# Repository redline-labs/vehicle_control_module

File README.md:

# Vehicle Control Module

A communication gateway and power distribution for motorsports, serving as the main electronic hub of the vehicle.

## Goals
  - Completely open-source HW and SW.  Should be a platform that anybody can hack, extend, and make their own.
  - Common parts, readily available for Digikey, Mouser, etc.  Datasheets are available without NDA.
  - Shoot for OEM level reliability and robustness, without going full ASIL alphabet soup.

## Vision
  - Controlling a circuit should be as simple as writing some logic `(engine_temp_c > 70.0f) && (vehicle_speed_mps < 5.0f)`.
  - No need for traditional fuses, relays as something like a slow-blow fuse can be done in software.
  - Plug into the vehicle using standard ethernet to debug/reconfigure/reflash.
  - Foundation for support datalogging, telemetry, and HMI.

## Hardware
Based on the Microchip [ATSAMV71Q21](https://www.microchip.com/wwwproducts/en/ATSAMV71Q21).
* (2) CAN-FD channels via [TLE9250](https://www.infineon.com/cms/en/product/transceivers/automotive-transceiver/automotive-can-transceivers/tle9250xsj/).
* (3) 100BASE-T1 channels via [TJA1100](https://www.nxp.com/products/interfaces/ethernet-/automotive-ethernet-phy-transceivers/ieee-100base-t1-compliant-automotive-ethernet-phy-transceiver:TJA1100HN).
* (1) 100BASE-TX channel via [KSZ8061MNX](https://www.microchip.com/wwwproducts/en/KSZ8061) to support debug with a laptop.
* (18) High Side drivers via [BTS50015-1TAD](https://www.infineon.com/cms/en/product/power/smart-low-side-high-side-switches/automotive-smart-high-side-switch-profet/power-profet/bts50015-1tad/).
* (2) RS-232 serial channels to connect GPS receivers and legacy IMUs.
* (8) Digital Inputs.

## Prerequisites
### MacOS
```
wget https://armkeil.blob.core.windows.net/developer/Files/downloads/gnu-rm/10-2020q2/gcc-arm-none-eabi-10-2020-q2-preview-mac.pkg

# Install.  Add `/Applications/ARM/bin/` to PATH via bash_profile.

brew install cmake
```

## Building
```
# Jump into the sw directory, create a build dir, and then jump into that.
cd sw
mkdir build
cd build

# Run CMake specifying the toolchain file.
cmake ..

# Build!
make
```

## Debugging
A configuration script under `conf/j-link` can be used with Segger Ozone to load the generated ELF on target and debug.

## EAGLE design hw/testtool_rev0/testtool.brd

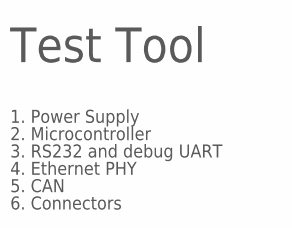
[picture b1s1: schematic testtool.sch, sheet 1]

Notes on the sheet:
Test Tool
1. Power Supply
2. Microcontroller
3. RS232 and debug UART
4. Ethernet PHY
5. CAN
6. Connectors

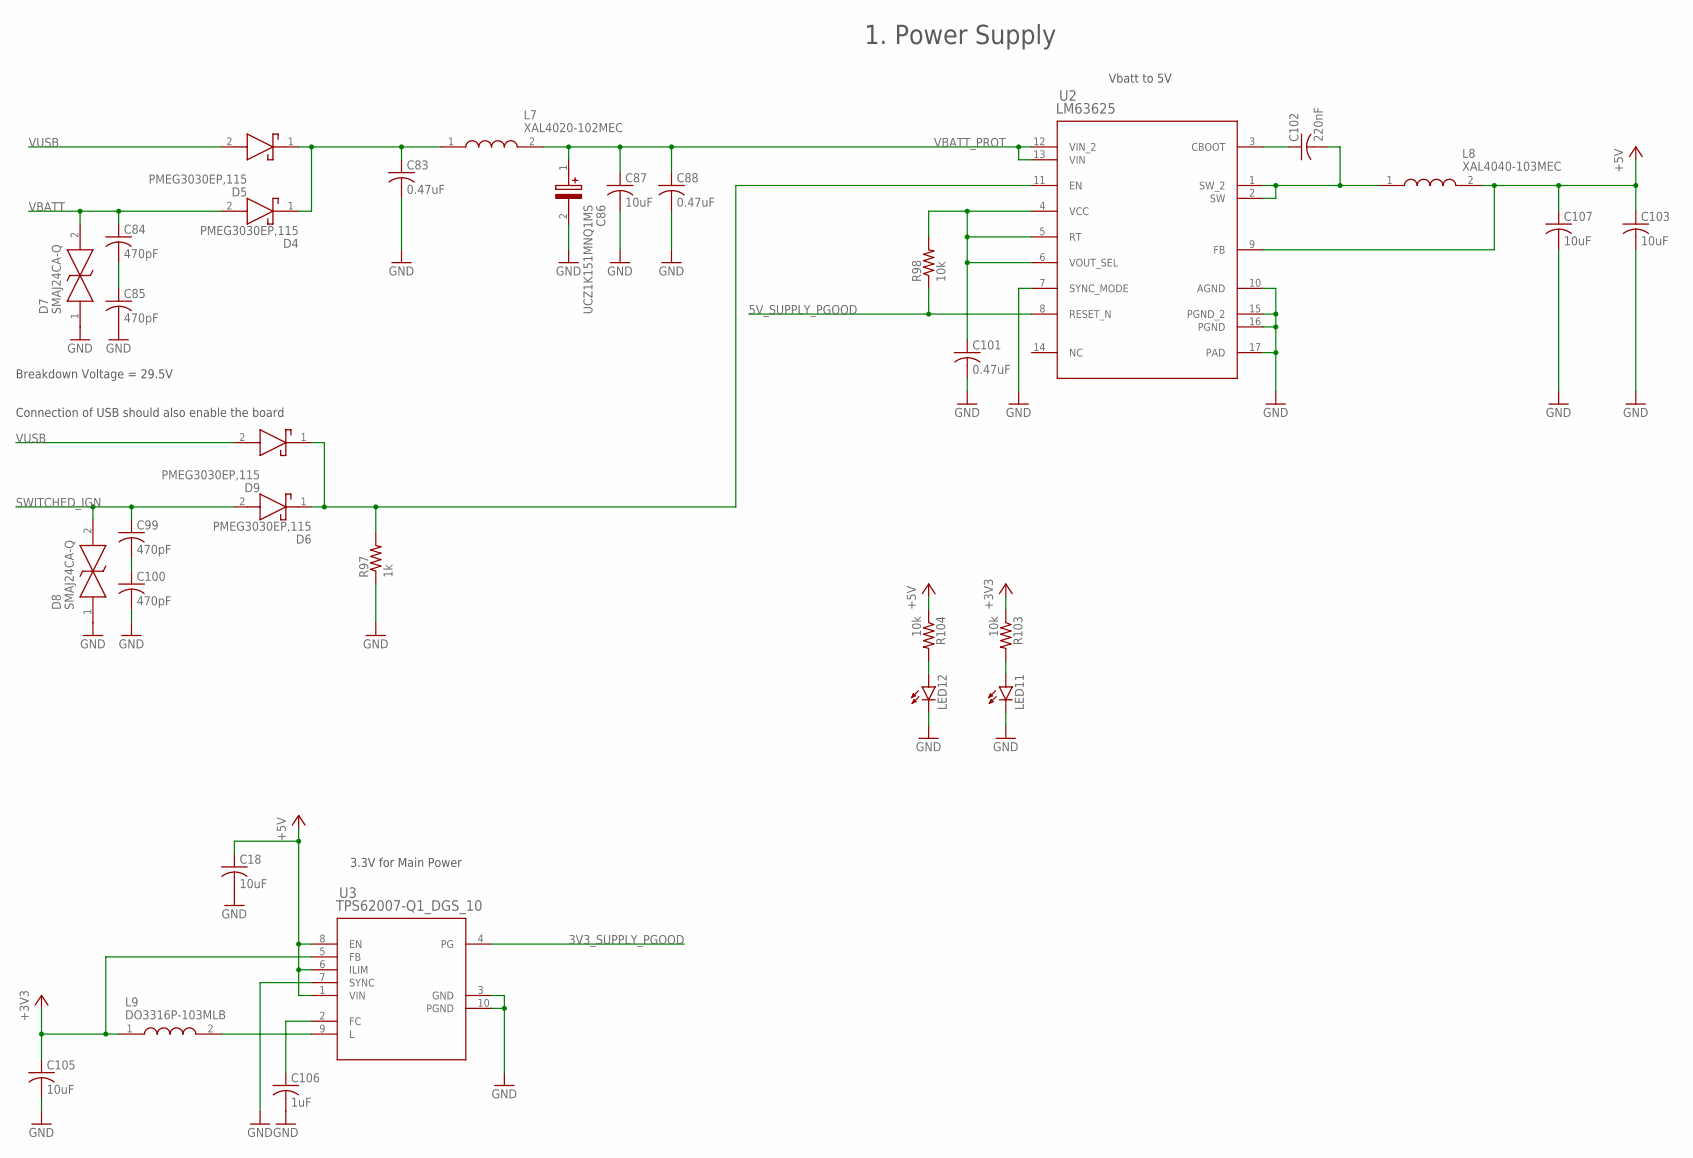
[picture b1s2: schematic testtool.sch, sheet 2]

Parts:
C18, C87, C103, C105, C107: 10uF; C0805
C83, C88: 0.47uF; C0805
C84, C85, C99, C100: 470pF; C0805
C86: UCZ1K151MNQ1MS; CAPAE1360X1450N
C101: 0.47uF; C0603
C102: 220nF; C0805
C106: 1uF; C0603
D4, D5, D6, D9: PMEG3030EP,115; SODFL4725X110N
D7, D8: SMAJ24CA-Q; DIONM5127X229N
L7: XAL4020-102MEC; XAL40XX
L8: XAL4040-103MEC; XAL40XX
L9: DO3316P-103MLB; DO3316P103MLB
LED11, LED12: LEDCHIPLED_0603; CHIPLED_0603
R97: 1k; R0805
R98, R103, R104: 10k; R0603
U2: LM63625; PWP0016K_L
U3: TPS62007-Q1_DGS_10; DGS10

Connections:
3V3_SUPPLY_PGOOD: U3.4 (PG); also elsewhere on the board
5V_SUPPLY_PGOOD: R98.1, U2.8 (RESET_N)
+3V3: C105.1, L9.1, R103.1, U3.5 (FB); also elsewhere on the board
+5V: C18.1, C103.1, C107.1, L8.2, R104.1, U2.9 (FB), U3.1 (VIN), U3.6 (ILIM), U3.8 (EN); also elsewhere on the board
GND: C18.2, C83.2, C85.2, C86.2 (-), C87.2, C88.2, C100.2, C101.2, C103.2, C105.2, C106.2, C107.2, D7.1, D8.1, LED11.C, LED12.C, R97.1, U2.7 (SYNC_MODE), U2.10 (AGND), U2.15 (PGND_2), U2.16 (PGND), U2.17 (PAD), U3.3 (GND), U3.7 (SYNC), U3.10 (PGND); also elsewhere on the board
unnamed: C99.2, C100.1
unnamed: D6.1 (K), D9.1 (K), R97.2, U2.11 (EN)
unnamed: C83.1, D4.1 (K), D5.1 (K), L7.1
unnamed: C84.2, C85.1
unnamed: C101.1, R98.2, U2.4 (VCC), U2.5 (RT), U2.6 (VOUT_SEL)
unnamed: L9.2, U3.9 (L)
unnamed: C102.2, L8.1, U2.1 (SW_2), U2.2 (SW)
unnamed: C106.1, U3.2 (FC)
unnamed: C102.1, U2.3 (CBOOT)
unnamed: LED11.A, R103.2
unnamed: LED12.A, R104.2
SWITCHED_IGN: C99.1, D6.2 (A), D8.2; also elsewhere on the board
VBATT: C84.1, D4.2 (A), D7.2; also elsewhere on the board
VBATT_PROT: C86.1 (+), C87.1, C88.1, L7.2, U2.12 (VIN_2), U2.13 (VIN)
VUSB: D5.2 (A), D9.2 (A); also elsewhere on the board

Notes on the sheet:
1. Power Supply
Vbatt to 5V
3.3V for Main Power
Breakdown Voltage = 29.5V
Connection of USB should also enable the board

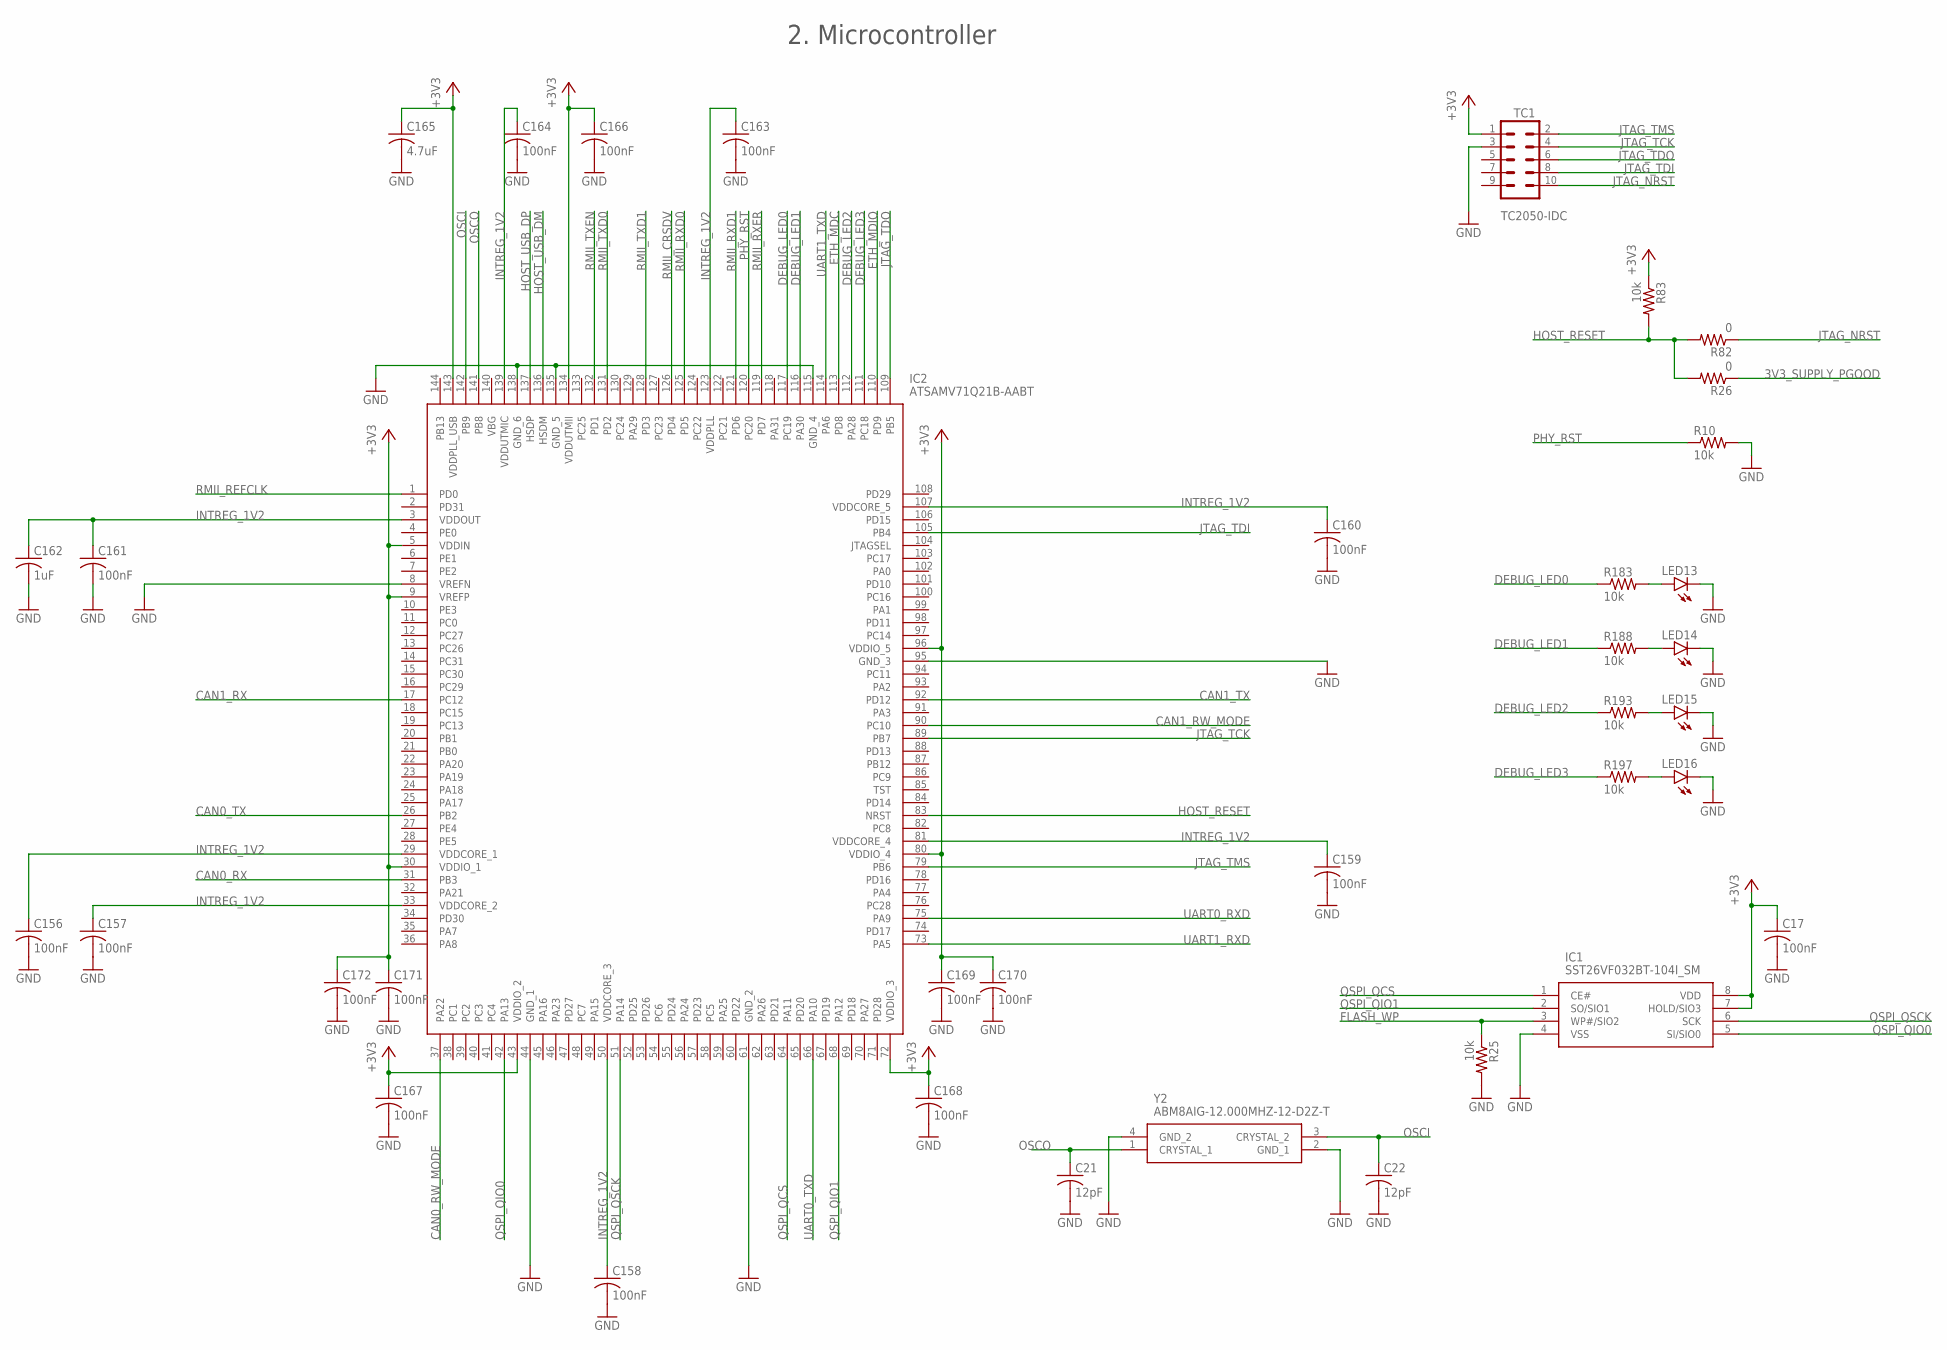
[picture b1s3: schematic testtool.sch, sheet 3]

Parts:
C17, C156, C157, C158, C159, C160, C161, C163, C164, C166, C167, C168, C169, C170, C171, C172: 100nF; C0603
C21, C22: 12pF; C0603
C162: 1uF; C0603
C165: 4.7uF; C0603
IC1: SST26VF032BT-104I_SM; SOIC127P794X203-8N
IC2: ATSAMV71Q21B-AABT; QFP50P2200X2200X160-144N
LED13, LED14, LED15, LED16: LEDCHIPLED_0603; CHIPLED_0603
R10, R25, R83, R183, R188, R193, R197: 10k; R0603
R26, R82: 0; R0603
TC1: TC2050-IDC
Y2: ABM8AIG-12.000MHZ-12-D2Z-T; ABM8AIG12000MHZ12D2ZT

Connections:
3V3_SUPPLY_PGOOD: R26.1; also elsewhere on the board
+3V3: C17.1, C165.1, C166.1, C167.1, C168.1, C169.1, C170.1, C171.1, C172.1, IC1.7 (HOLD/SIO3), IC1.8 (VDD), IC2.5 (VDDIN), IC2.9 (VREFP), IC2.30 (VDDIO_1), IC2.43 (VDDIO_2), IC2.72 (VDDIO_3), IC2.80 (VDDIO_4), IC2.96 (VDDIO_5), IC2.134 (VDDUTMII), IC2.143 (VDDPLL_USB), R83.1, TC1.1; also elsewhere on the board
CAN0_RW_MODE: IC2.37 (PA22); also elsewhere on the board
CAN0_RX: IC2.31 (PB3); also elsewhere on the board
CAN0_TX: IC2.26 (PB2); also elsewhere on the board
CAN1_RW_MODE: IC2.90 (PC10); also elsewhere on the board
CAN1_RX: IC2.17 (PC12); also elsewhere on the board
CAN1_TX: IC2.92 (PD12); also elsewhere on the board
DEBUG_LED0: IC2.117 (PC19), R183.1
DEBUG_LED1: IC2.116 (PA30), R188.1
DEBUG_LED2: IC2.112 (PA28), R193.1
DEBUG_LED3: IC2.111 (PC18), R197.1
ETH_MDC: IC2.113 (PD8); also elsewhere on the board
ETH_MDIO: IC2.110 (PD9); also elsewhere on the board
FLASH_WP: IC1.3 (WP#/SIO2), R25.1
GND: C17.2, C21.2, C22.2, C156.2, C157.2, C158.2, C159.2, C160.2, C161.2, C162.2, C163.2, C164.2, C165.2, C166.2, C167.2, C168.2, C169.2, C170.2, C171.2, C172.2, IC1.4 (VSS), IC2.8 (VREFN), IC2.44 (GND_1), IC2.61 (GND_2), IC2.95 (GND_3), IC2.115 (GND_4), IC2.135 (GND_5), IC2.138 (GND_6), LED13.C, LED14.C, LED15.C, LED16.C, R10.2, R25.2, TC1.3, Y2.2 (GND_1), Y2.4 (GND_2); also elsewhere on the board
HOST_RESET: IC2.83 (NRST), R26.2, R82.2, R83.2
HOST_USB_DM: IC2.136 (HSDM); also elsewhere on the board
HOST_USB_DP: IC2.137 (HSDP); also elsewhere on the board
INTREG_1V2: C156.1, C157.1, C158.1, C159.1, C160.1, C161.1, C162.1, C163.1, C164.1, IC2.3 (VDDOUT), IC2.29 (VDDCORE_1), IC2.33 (VDDCORE_2), IC2.50 (VDDCORE_3), IC2.81 (VDDCORE_4), IC2.107 (VDDCORE_5), IC2.123 (VDDPLL), IC2.139 (VDDUTMIC)
JTAG_NRST: R82.1, TC1.10
JTAG_TCK: IC2.89 (PB7), TC1.4
JTAG_TDI: IC2.105 (PB4), TC1.8
JTAG_TDO: IC2.109 (PB5), TC1.6
JTAG_TMS: IC2.79 (PB6), TC1.2
unnamed: LED13.A, R183.2
unnamed: LED14.A, R188.2
unnamed: LED15.A, R193.2
unnamed: LED16.A, R197.2
OSCI: C22.1, IC2.142 (PB9), Y2.3 (CRYSTAL_2)
OSCO: C21.1, IC2.141 (PB8), Y2.1 (CRYSTAL_1)
PHY_RST: IC2.120 (PC20), R10.1; also elsewhere on the board
QSPI_QCS: IC1.1 (CE#), IC2.64 (PA11)
QSPI_QIO0: IC1.5 (SI/SIO0), IC2.42 (PA13)
QSPI_QIO1: IC1.2 (SO/SIO1), IC2.68 (PA12)
QSPI_QSCK: IC1.6 (SCK), IC2.51 (PA14)
RMII_CRSDV: IC2.126 (PD4); also elsewhere on the board
RMII_REFCLK: IC2.1 (PD0); also elsewhere on the board
RMII_RXD0: IC2.125 (PD5); also elsewhere on the board
RMII_RXD1: IC2.121 (PD6); also elsewhere on the board
RMII_RXER: IC2.119 (PD7); also elsewhere on the board
RMII_TXD0: IC2.131 (PD2); also elsewhere on the board
RMII_TXD1: IC2.128 (PD3); also elsewhere on the board
RMII_TXEN: IC2.132 (PD1); also elsewhere on the board
UART0_RXD: IC2.75 (PA9); also elsewhere on the board
UART0_TXD: IC2.66 (PA10); also elsewhere on the board
UART1_RXD: IC2.73 (PA5); also elsewhere on the board
UART1_TXD: IC2.114 (PA6); also elsewhere on the board

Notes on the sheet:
2. Microcontroller

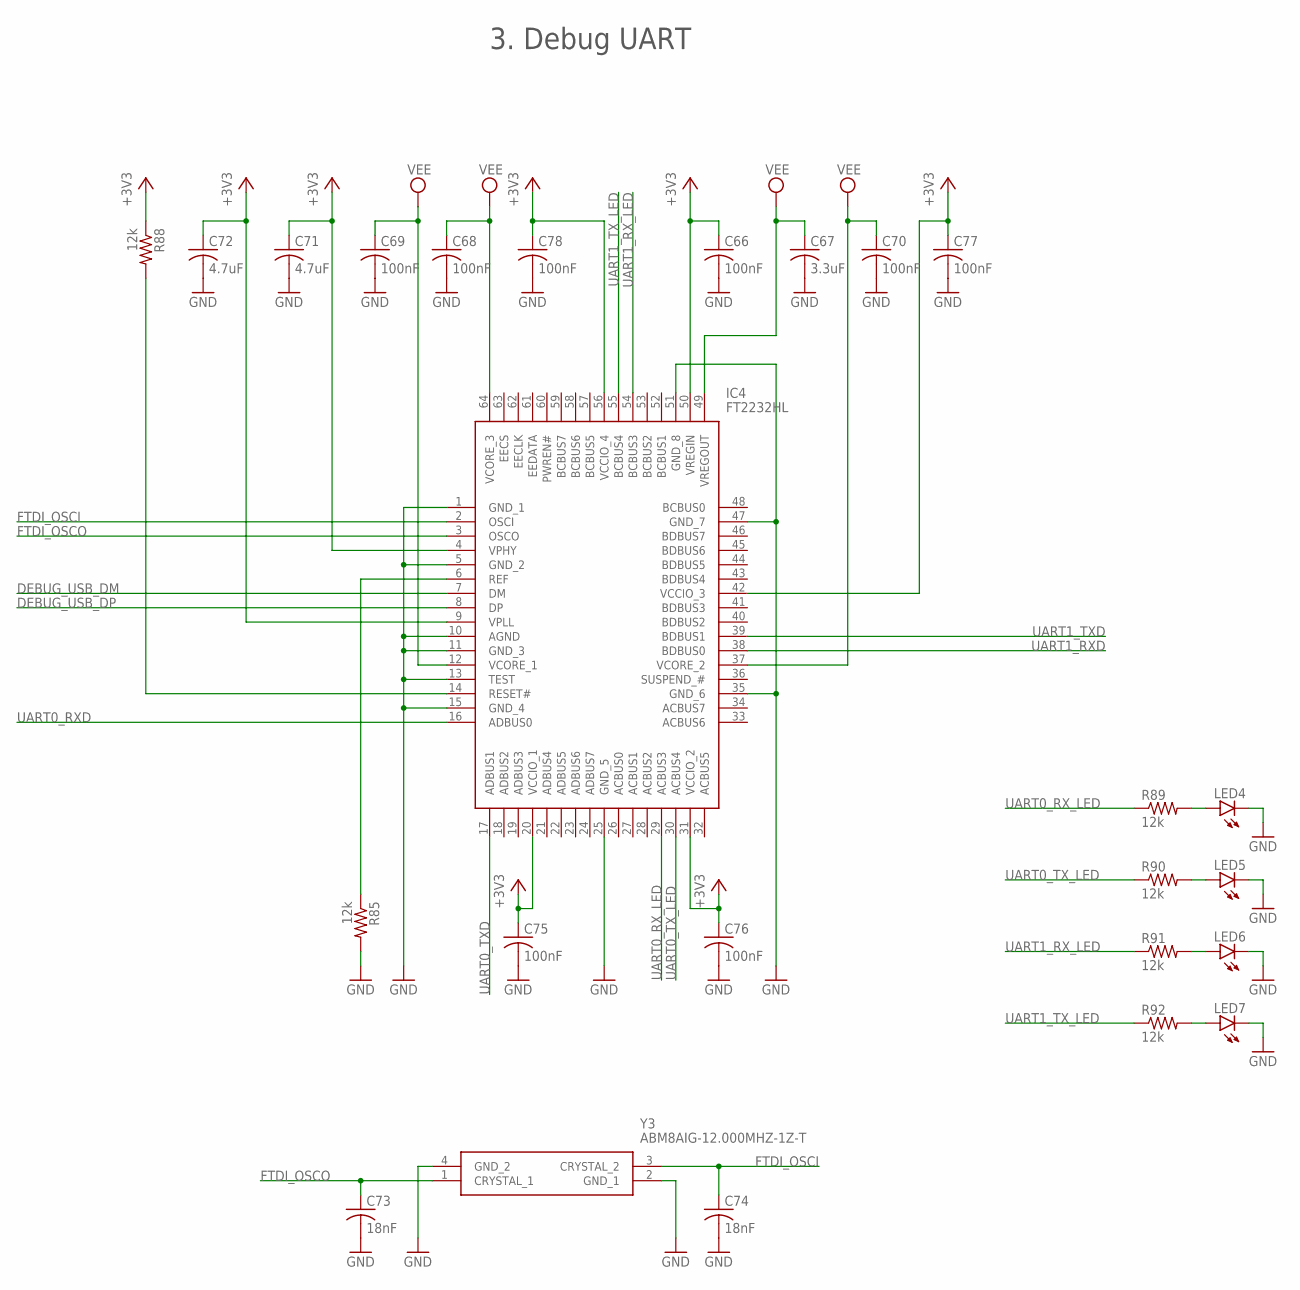
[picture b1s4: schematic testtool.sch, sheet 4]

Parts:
C66, C68, C69, C70, C75, C76, C77, C78: 100nF; C0603
C67: 3.3uF; C0603
C71, C72: 4.7uF; C0603
C73, C74: 18nF; C0603
IC4: FT2232HL; QFP50P1200X1200X160-64N
LED4, LED5, LED6, LED7: LEDCHIPLED_0603; CHIPLED_0603
R85, R88, R89, R90, R91, R92: 12k; R0603
Y3: ABM8AIG-12.000MHZ-1Z-T; ABM8AIG25000MHZ122ZT3

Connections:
+3V3: C66.1, C71.1, C72.1, C75.1, C76.1, C77.1, C78.1, IC4.4 (VPHY), IC4.9 (VPLL), IC4.20 (VCCIO_1), IC4.31 (VCCIO_2), IC4.42 (VCCIO_3), IC4.50 (VREGIN), IC4.56 (VCCIO_4), R88.1; also elsewhere on the board
DEBUG_USB_DM: IC4.7 (DM); also elsewhere on the board
DEBUG_USB_DP: IC4.8 (DP); also elsewhere on the board
FTDI_OSCI: C74.1, IC4.2 (OSCI), Y3.3 (CRYSTAL_2)
FTDI_OSCO: C73.1, IC4.3 (OSCO), Y3.1 (CRYSTAL_1)
GND: C66.2, C67.2, C68.2, C69.2, C70.2, C71.2, C72.2, C73.2, C74.2, C75.2, C76.2, C77.2, C78.2, IC4.1 (GND_1), IC4.5 (GND_2), IC4.10 (AGND), IC4.11 (GND_3), IC4.13 (TEST), IC4.15 (GND_4), IC4.25 (GND_5), IC4.35 (GND_6), IC4.47 (GND_7), IC4.51 (GND_8), LED4.C, LED5.C, LED6.C, LED7.C, R85.2, Y3.2 (GND_1), Y3.4 (GND_2); also elsewhere on the board
unnamed: IC4.6 (REF), R85.1
unnamed: IC4.14 (RESET#), R88.2
unnamed: LED5.A, R90.2
unnamed: LED4.A, R89.2
unnamed: LED6.A, R91.2
unnamed: LED7.A, R92.2
UART0_RXD: IC4.16 (ADBUS0); also elsewhere on the board
UART0_RX_LED: IC4.29 (ACBUS3), R89.1
UART0_TXD: IC4.17 (ADBUS1); also elsewhere on the board
UART0_TX_LED: IC4.30 (ACBUS4), R90.1
UART1_RXD: IC4.38 (BDBUS0); also elsewhere on the board
UART1_RX_LED: IC4.54 (BCBUS3), R91.1
UART1_TXD: IC4.39 (BDBUS1); also elsewhere on the board
UART1_TX_LED: IC4.55 (BCBUS4), R92.1
VEE: C67.1, C68.1, C69.1, C70.1, IC4.12 (VCORE_1), IC4.37 (VCORE_2), IC4.49 (VREGOUT), IC4.64 (VCORE_3)

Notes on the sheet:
3. Debug UART

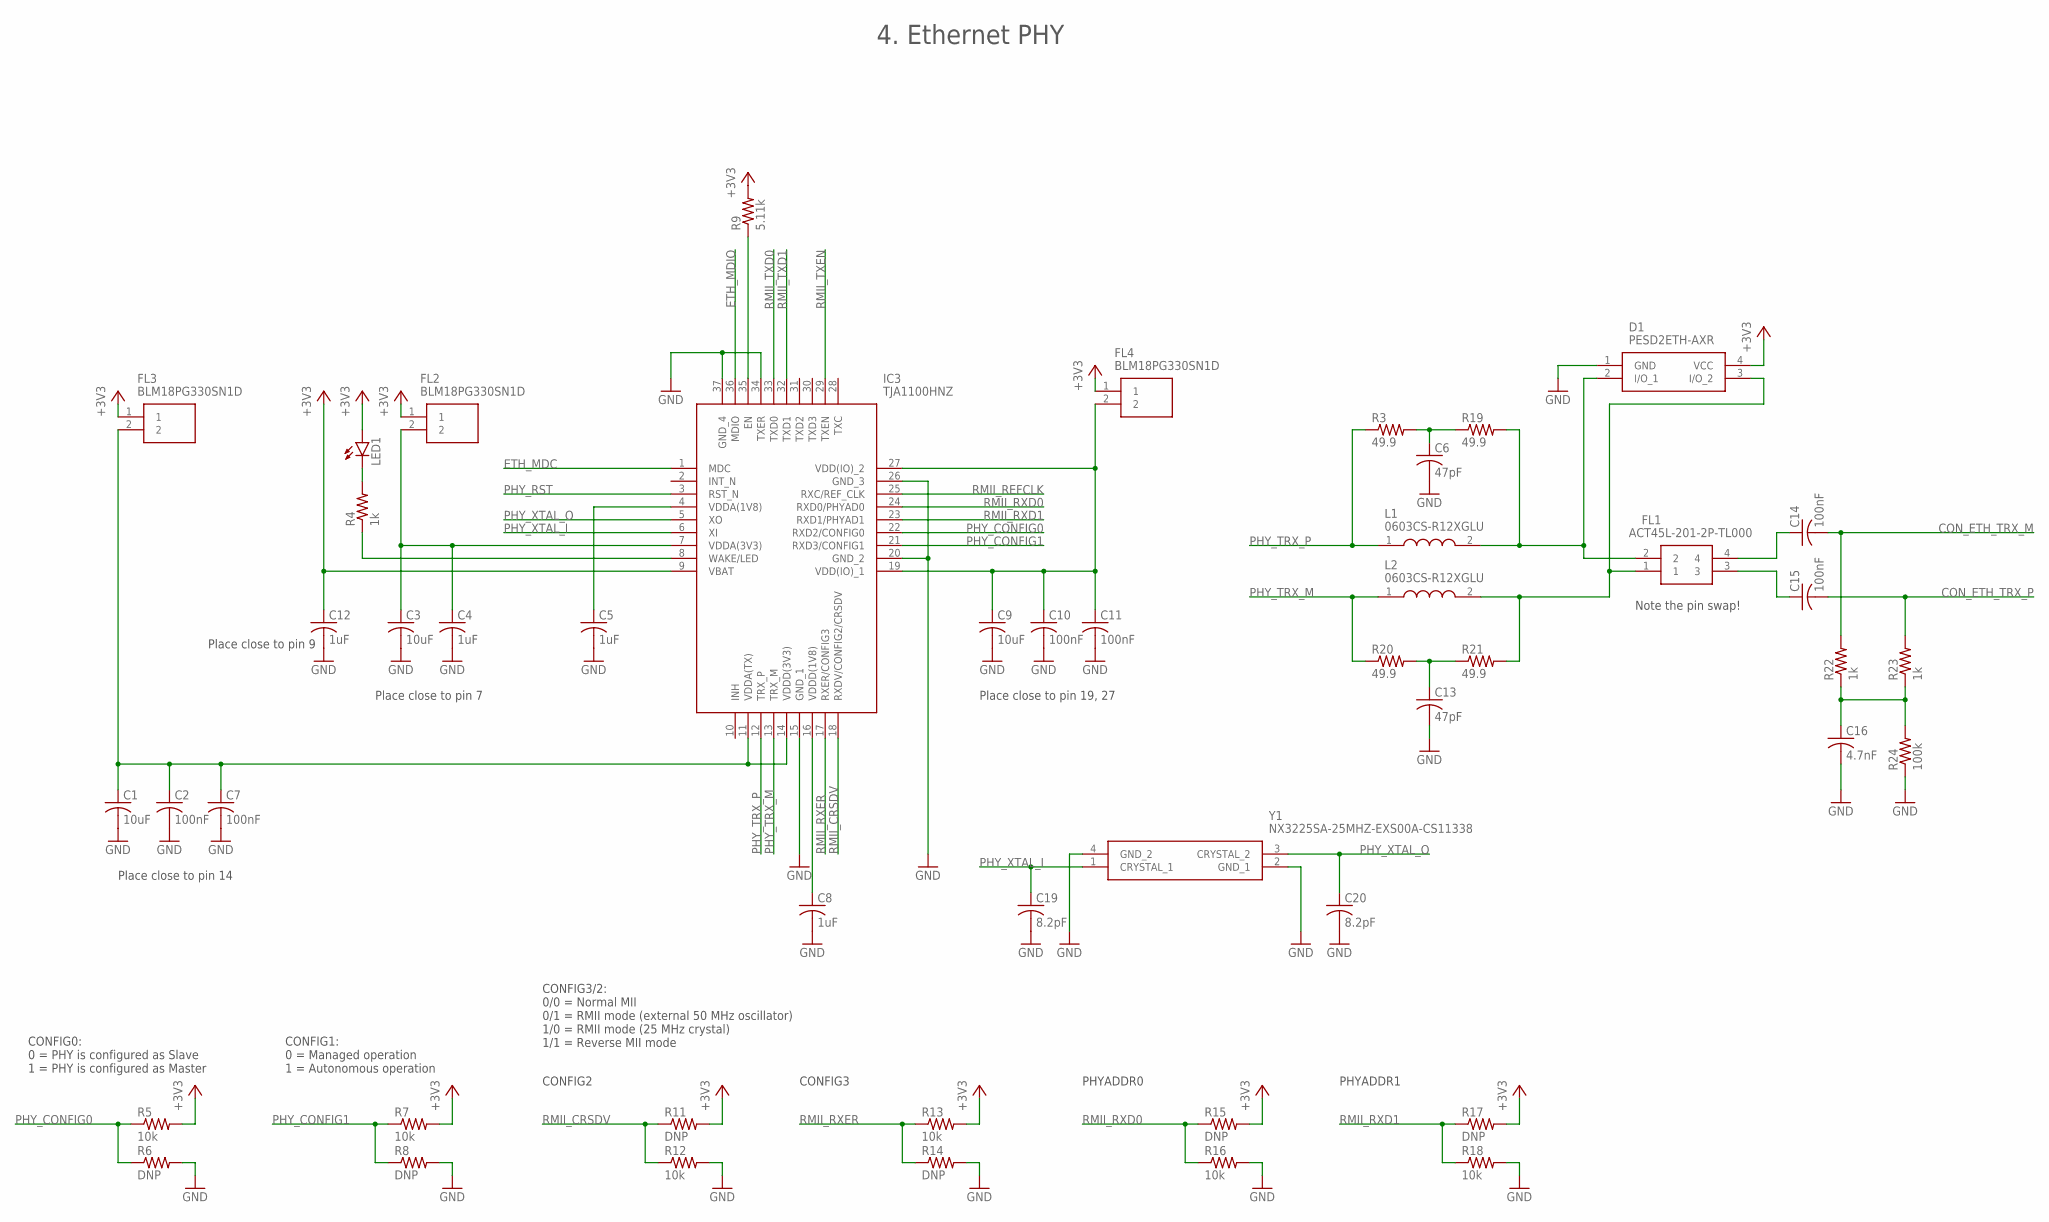
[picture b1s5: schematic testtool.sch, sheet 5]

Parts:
C1, C3, C9: 10uF; C0603
C2, C7, C10, C11, C14, C15: 100nF; C0603
C4, C5, C8, C12: 1uF; C0603
C6, C13: 47pF; C0603
C16: 4.7nF; C0603
C19, C20: 8.2pF; C0603
D1: PESD2ETH-AXR; PESD2ETHAXR
FL1: ACT45L-201-2P-TL000; ACT45L_1
FL2, FL3, FL4: BLM18PG330SN1D; BEADC1608X95N
IC3: TJA1100HNZ; QFN50P600X600X100-37N
L1, L2: 0603CS-R12XGLU; 0603CS82NXGLW
LED1: LEDCHIPLED_0603; CHIPLED_0603
R3, R19, R20, R21: 49.9; R0603
R4, R22, R23: 1k; R0603
R5, R7, R12, R13, R16, R18: 10k; R0603
R6, R8, R11, R14, R15, R17: DNP; R0603
R9: 5.11k; R0603
R24: 100k; R0603
Y1: NX3225SA-25MHZ-EXS00A-CS11338; NX3225SA25MHZEXS00ACS11338

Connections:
+3V3: C12.1, D1.4 (VCC), FL2.1, FL3.1, FL4.1, IC3.9 (VBAT), LED1.A, R5.2, R7.2, R9.2, R11.2, R13.2, R15.2, R17.2; also elsewhere on the board
CON_ETH_TRX_M: C14.2, R22.2; also elsewhere on the board
CON_ETH_TRX_P: C15.2, R23.2; also elsewhere on the board
ETH_MDC: IC3.1 (MDC); also elsewhere on the board
ETH_MDIO: IC3.36 (MDIO); also elsewhere on the board
GND: C1.2, C2.2, C3.2, C4.2, C5.2, C6.2, C7.2, C8.2, C9.2, C10.2, C11.2, C12.2, C13.2, C16.2, C19.2, C20.2, D1.1 (GND), IC3.15 (GND_1), IC3.20 (GND_2), IC3.26 (GND_3), IC3.34 (TXER), IC3.37 (GND_4), R6.2, R8.2, R12.2, R14.2, R16.2, R18.2, R24.1, Y1.2 (GND_1), Y1.4 (GND_2); also elsewhere on the board
unnamed: LED1.C, R4.2
unnamed: C5.1, IC3.4 (VDDA(1V8))
unnamed: IC3.8 (WAKE/LED), R4.1
unnamed: C8.1, IC3.16 (VDDD(1V8))
unnamed: C3.1, C4.1, FL2.2, IC3.7 (VDDA(3V3))
unnamed: C1.1, C2.1, C7.1, FL3.2, IC3.11 (VDDA(TX)), IC3.14 (VDDD(3V3))
unnamed: C9.1, C10.1, C11.1, FL4.2, IC3.19 (VDD(IO)_1), IC3.27 (VDD(IO)_2)
unnamed: IC3.35 (EN), R9.1
unnamed: D1.3 (I/O_2), FL1.1, L2.2, R21.2
unnamed: D1.2 (I/O_1), FL1.2, L1.2, R19.2
unnamed: C6.1, R3.2, R19.1
unnamed: C13.1, R20.2, R21.1
unnamed: C14.1, FL1.4
unnamed: C15.1, FL1.3
unnamed: C16.1, R22.1, R23.1, R24.2
PHY_CONFIG0: IC3.22 (RXD2/CONFIG0), R5.1, R6.1
PHY_CONFIG1: IC3.21 (RXD3/CONFIG1), R7.1, R8.1
PHY_RST: IC3.3 (RST_N); also elsewhere on the board
PHY_TRX_M: IC3.13 (TRX_M), L2.1, R20.1
PHY_TRX_P: IC3.12 (TRX_P), L1.1, R3.1
PHY_XTAL_I: C19.1, IC3.6 (XI), Y1.1 (CRYSTAL_1)
PHY_XTAL_O: C20.1, IC3.5 (XO), Y1.3 (CRYSTAL_2)
RMII_CRSDV: IC3.18 (RXDV/CONFIG2/CRSDV), R11.1, R12.1; also elsewhere on the board
RMII_REFCLK: IC3.25 (RXC/REF_CLK); also elsewhere on the board
RMII_RXD0: IC3.24 (RXD0/PHYAD0), R15.1, R16.1; also elsewhere on the board
RMII_RXD1: IC3.23 (RXD1/PHYAD1), R17.1, R18.1; also elsewhere on the board
RMII_RXER: IC3.17 (RXER/CONFIG3), R13.1, R14.1; also elsewhere on the board
RMII_TXD0: IC3.33 (TXD0); also elsewhere on the board
RMII_TXD1: IC3.32 (TXD1); also elsewhere on the board
RMII_TXEN: IC3.29 (TXEN); also elsewhere on the board

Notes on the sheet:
Place close to pin 7
Place close to pin 9
Place close to pin 14
Place close to pin 19, 27
CONFIG0: 0 = PHY is configured as Slave 1 = PHY is configured as Master
CONFIG1: 0 = Managed operation 1 = Autonomous operation
Note the pin swap!
4. Ethernet PHY
CONFIG3/2: 0/0 = Normal MII 0/1 = RMII mode (external 50 MHz oscillator) 1/0 = RMII mode (25 MHz crystal) 1/1 = Reverse MII mode
CONFIG2
CONFIG3
PHYADDR0
PHYADDR1

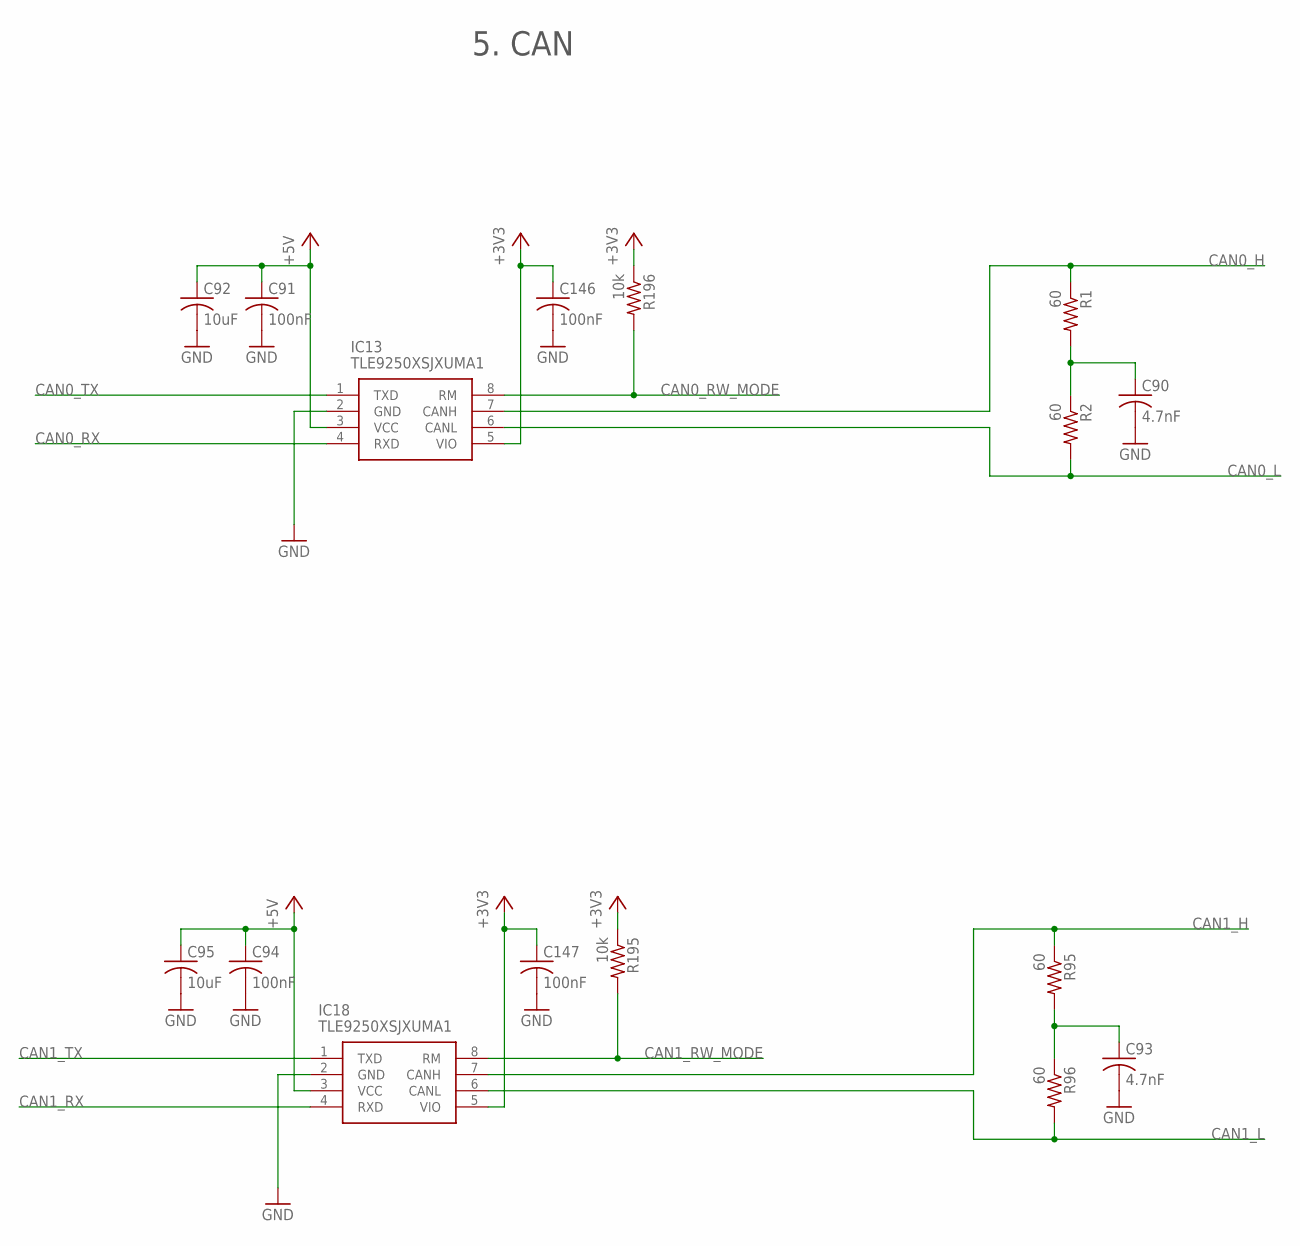
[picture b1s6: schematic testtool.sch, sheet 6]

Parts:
C90, C93: 4.7nF; C0603
C91, C94, C146, C147: 100nF; C0603
C92, C95: 10uF; C0603
IC13, IC18: TLE9250XSJXUMA1; SOIC127P602X173-8N
R1, R2, R95, R96: 60; R0805
R195, R196: 10k; R0603

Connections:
+3V3: C146.1, C147.1, IC13.5 (VIO), IC18.5 (VIO), R195.1, R196.1; also elsewhere on the board
+5V: C91.1, C92.1, C94.1, C95.1, IC13.3 (VCC), IC18.3 (VCC); also elsewhere on the board
CAN0_H: IC13.7 (CANH), R1.1; also elsewhere on the board
CAN0_L: IC13.6 (CANL), R2.2; also elsewhere on the board
CAN0_RW_MODE: IC13.8 (RM), R196.2; also elsewhere on the board
CAN0_RX: IC13.4 (RXD); also elsewhere on the board
CAN0_TX: IC13.1 (TXD); also elsewhere on the board
CAN1_H: IC18.7 (CANH), R95.1; also elsewhere on the board
CAN1_L: IC18.6 (CANL), R96.2; also elsewhere on the board
CAN1_RW_MODE: IC18.8 (RM), R195.2; also elsewhere on the board
CAN1_RX: IC18.4 (RXD); also elsewhere on the board
CAN1_TX: IC18.1 (TXD); also elsewhere on the board
GND: C90.2, C91.2, C92.2, C93.2, C94.2, C95.2, C146.2, C147.2, IC13.2 (GND), IC18.2 (GND); also elsewhere on the board
unnamed: C93.1, R95.2, R96.1
unnamed: C90.1, R1.2, R2.1

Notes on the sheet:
5. CAN

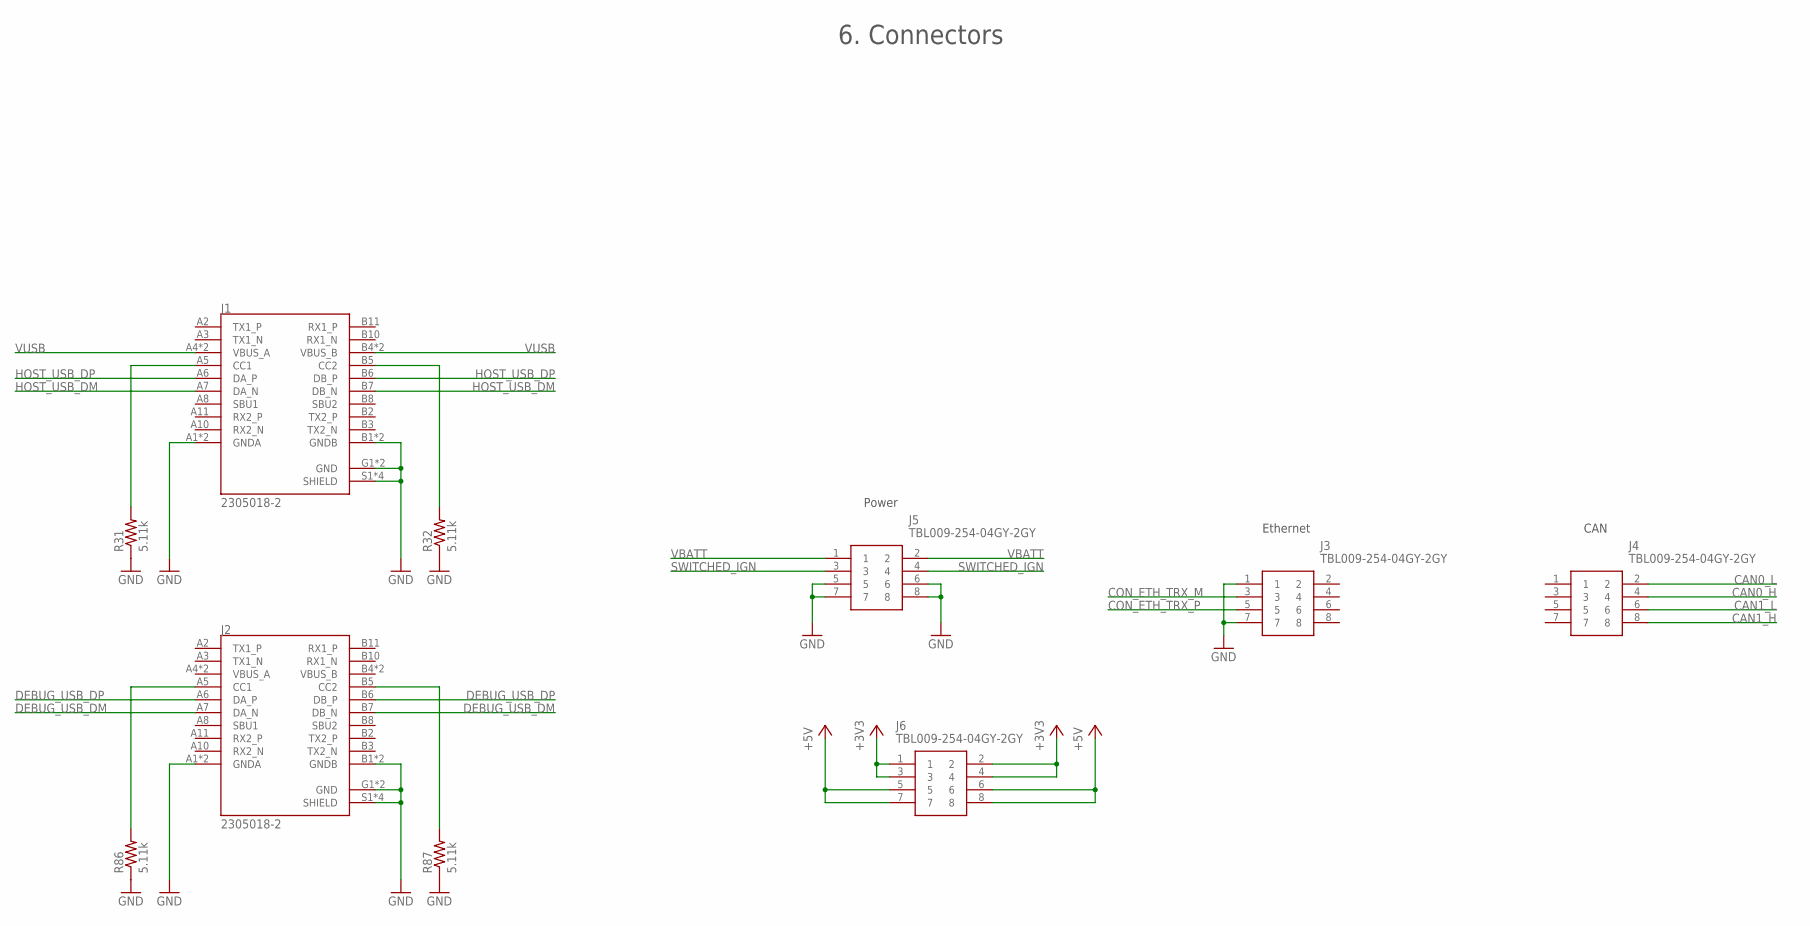
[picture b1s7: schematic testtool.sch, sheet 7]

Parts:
J1, J2: 2305018-2; TE_2305018-2
J3, J4, J5, J6: TBL009-254-04GY-2GY; TBL00925404GY2GY
R31, R32, R86, R87: 5.11k; R0603

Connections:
+3V3: J6.1, J6.2, J6.3, J6.4; also elsewhere on the board
+5V: J6.5, J6.6, J6.7, J6.8; also elsewhere on the board
CAN0_H: J4.4; also elsewhere on the board
CAN0_L: J4.2; also elsewhere on the board
CAN1_H: J4.8; also elsewhere on the board
CAN1_L: J4.6; also elsewhere on the board
CON_ETH_TRX_M: J3.3; also elsewhere on the board
CON_ETH_TRX_P: J3.5; also elsewhere on the board
DEBUG_USB_DM: J2.A7 (DA_N), J2.B7 (DB_N); also elsewhere on the board
DEBUG_USB_DP: J2.A6 (DA_P), J2.B6 (DB_P); also elsewhere on the board
GND: J1.A1 (GNDA), J1.A12 (GNDA), J1.B1 (GNDB), J1.B12 (GNDB), J1.G1 (GND), J1.G2 (GND), J1.S1 (SHIELD), J1.S2 (SHIELD), J1.S3 (SHIELD), J1.S4 (SHIELD), J2.A1 (GNDA), J2.A12 (GNDA), J2.B1 (GNDB), J2.B12 (GNDB), J2.G1 (GND), J2.G2 (GND), J2.S1 (SHIELD), J2.S2 (SHIELD), J2.S3 (SHIELD), J2.S4 (SHIELD), J3.1, J3.7, J5.5, J5.6, J5.7, J5.8, R31.1, R32.1, R86.1, R87.1; also elsewhere on the board
HOST_USB_DM: J1.A7 (DA_N), J1.B7 (DB_N); also elsewhere on the board
HOST_USB_DP: J1.A6 (DA_P), J1.B6 (DB_P); also elsewhere on the board
unnamed: J1.A5 (CC1), R31.2
unnamed: J1.B5 (CC2), R32.2
unnamed: J2.A5 (CC1), R86.2
unnamed: J2.B5 (CC2), R87.2
SWITCHED_IGN: J5.3, J5.4; also elsewhere on the board
VBATT: J5.1, J5.2; also elsewhere on the board
VUSB: J1.A4 (VBUS_A), J1.A9 (VBUS_A), J1.B4 (VBUS_B), J1.B9 (VBUS_B); also elsewhere on the board

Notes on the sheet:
Power
Ethernet
CAN
6. Connectors

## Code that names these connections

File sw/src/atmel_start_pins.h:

/*
 * Code generated from Atmel Start.
 *
 * This file will be overwritten when reconfiguring your Atmel Start project.
 * Please copy examples or other code you want to keep to a separate file
 * to avoid losing it when reconfiguring.
 */
#ifndef ATMEL_START_PINS_H_INCLUDED
#define ATMEL_START_PINS_H_INCLUDED

#include <hal_gpio.h>

// SAMV71 has 4 pin functions

#define GPIO_PIN_FUNCTION_A 0
#define GPIO_PIN_FUNCTION_B 1
#define GPIO_PIN_FUNCTION_C 2
#define GPIO_PIN_FUNCTION_D 3

#define PA0 GPIO(GPIO_PORTA, 0)
#define PA2 GPIO(GPIO_PORTA, 2)
#define PA3 GPIO(GPIO_PORTA, 3)
#define PA4 GPIO(GPIO_PORTA, 4)
#define PA5 GPIO(GPIO_PORTA, 5)
#define PA6 GPIO(GPIO_PORTA, 6)
#define PA7 GPIO(GPIO_PORTA, 7)
#define PA8 GPIO(GPIO_PORTA, 8)
#define PA9 GPIO(GPIO_PORTA, 9)
#define PA10 GPIO(GPIO_PORTA, 10)
#define PA11 GPIO(GPIO_PORTA, 11)
#define PA12 GPIO(GPIO_PORTA, 12)
#define PA13 GPIO(GPIO_PORTA, 13)
#define PA14 GPIO(GPIO_PORTA, 14)
#define PA17 GPIO(GPIO_PORTA, 17)
#define PA18 GPIO(GPIO_PORTA, 18)
#define PA19 GPIO(GPIO_PORTA, 19)
#define PA20 GPIO(GPIO_PORTA, 20)
#define PA21 GPIO(GPIO_PORTA, 21)
#define PA23 GPIO(GPIO_PORTA, 23)
#define PA25 GPIO(GPIO_PORTA, 25)
#define PA31 GPIO(GPIO_PORTA, 31)
#define PB0 GPIO(GPIO_PORTB, 0)
#define PB1 GPIO(GPIO_PORTB, 1)
#define PB2 GPIO(GPIO_PORTB, 2)
#define PB3 GPIO(GPIO_PORTB, 3)
#define PB4 GPIO(GPIO_PORTB, 4)
#define PC0 GPIO(GPIO_PORTC, 0)
#define PC12 GPIO(GPIO_PORTC, 12)
#define PC13 GPIO(GPIO_PORTC, 13)
#define PC15 GPIO(GPIO_PORTC, 15)
#define PC26 GPIO(GPIO_PORTC, 26)
#define PC27 GPIO(GPIO_PORTC, 27)
#define PC29 GPIO(GPIO_PORTC, 29)
#define PC30 GPIO(GPIO_PORTC, 30)
#define PC31 GPIO(GPIO_PORTC, 31)
#define PD0 GPIO(GPIO_PORTD, 0)
#define PD1 GPIO(GPIO_PORTD, 1)
#define PD2 GPIO(GPIO_PORTD, 2)
#define PD3 GPIO(GPIO_PORTD, 3)
#define PD4 GPIO(GPIO_PORTD, 4)
#define PD5 GPIO(GPIO_PORTD, 5)
#define PD6 GPIO(GPIO_PORTD, 6)
#define PD7 GPIO(GPIO_PORTD, 7)
#define PD8 GPIO(GPIO_PORTD, 8)
#define PD9 GPIO(GPIO_PORTD, 9)
#define PD11 GPIO(GPIO_PORTD, 11)
#define PD12 GPIO(GPIO_PORTD, 12)
#define PD20 GPIO(GPIO_PORTD, 20)
#define PD21 GPIO(GPIO_PORTD, 21)
#define PD22 GPIO(GPIO_PORTD, 22)
#define PD25 GPIO(GPIO_PORTD, 25)
#define PD26 GPIO(GPIO_PORTD, 26)
#define PD28 GPIO(GPIO_PORTD, 28)
#define PD30 GPIO(GPIO_PORTD, 30)
#define PD31 GPIO(GPIO_PORTD, 31)
#define PE0 GPIO(GPIO_PORTE, 0)
#define PE3 GPIO(GPIO_PORTE, 3)
#define PE4 GPIO(GPIO_PORTE, 4)
#define PE5 GPIO(GPIO_PORTE, 5)

#define LED0 GPIO(GPIO_PORTC, 19)
#define LED1 GPIO(GPIO_PORTA, 30)
#define LED2 GPIO(GPIO_PORTA, 28)
#define LED3 GPIO(GPIO_PORTC, 18)

#define CAN0_RW_MODE GPIO(GPIO_PORTA, 22)
#define CAN1_RW_MODE GPIO(GPIO_PORTC, 10)

#endif // ATMEL_START_PINS_H_INCLUDED

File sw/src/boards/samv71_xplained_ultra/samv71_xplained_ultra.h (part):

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
#define CONSOLE_UART               USART1
#define CONSOLE_UART_ID            ID_USART1
/** USART1 pins definitions, PA21,PB4. */
#define USART1_RXD_GPIO   PIO_PA21_IDX
#define USART1_RXD_FLAGS  IOPORT_MODE_MUX_A
#define USART1_TXD_GPIO   PIO_PB4_IDX
#define USART1_TXD_FLAGS  IOPORT_MODE_MUX_D

/** USART0 pins definitions, PB0,PB1. */
#define USART0_RXD_GPIO   PIO_PB0_IDX
#define USART0_RXD_FLAGS  IOPORT_MODE_MUX_C
#define USART0_TXD_GPIO   PIO_PB1_IDX
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#define EXT2_PIN_SPI_SCK          EXT2_PIN_18
//@}

/** PCK0 pin definition (PA6) */
#define PIN_PCK0         (PIO_PA6_IDX)
#define PIN_PCK0_MUX     (IOPORT_MODE_MUX_B)
#define PIN_PCK0_FLAGS   (IOPORT_MODE_MUX_B)
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#define TWIHS0_CLK_FLAGS   (IOPORT_MODE_MUX_A)

/** SPI0 pins definition */
#define SPI0_MISO_GPIO    PIO_PD20_IDX
#define SPI0_MISO_FLAGS  (IOPORT_MODE_MUX_B)
#define SPI0_MOSI_GPIO    PIO_PD21_IDX
#define SPI0_MOSI_FLAGS  (IOPORT_MODE_MUX_B)
#define SPI0_NPCS0_GPIO   PIO_PB2_IDX
#define SPI0_NPCS0_FLAGS  (IOPORT_MODE_MUX_D)
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#define SPI0_SPCK_FLAGS  (IOPORT_MODE_MUX_B)

/** QSPI pins definition */
#define QSPI_QSCK_GPIO    PIO_PA14_IDX
#define QSPI_QSCK_FLAGS   (IOPORT_MODE_MUX_A)
#define QSPI_QCS_GPIO     PIO_PA11_IDX
#define QSPI_QCS_FLAGS    (IOPORT_MODE_MUX_A)
#define QSPI_QIO0_GPIO    PIO_PA13_IDX
#define QSPI_QIO0_FLAGS   (IOPORT_MODE_MUX_A)
#define QSPI_QIO1_GPIO    PIO_PA12_IDX
#define QSPI_QIO1_FLAGS   (IOPORT_MODE_MUX_A)
#define QSPI_QIO2_GPIO    PIO_PA17_IDX
#define QSPI_QIO2_FLAGS   (IOPORT_MODE_MUX_A)
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#define PIN_PWM_LED1_CHANNEL PWM_CHANNEL_1

// Highside 0 pin definitions.
// Net ADC0_3 -> PE05 -> J504 Analog High, Pin 4 (AD11), AFE0_AD3
// Net HIGHSIDE_0_EN -> PD11 -> J503 Digital Low, Pin 6 (D5), PWMC0_PWMH0
#define PIN_HIGHSIDE0_EN_GPIO           (PIO_PD11_IDX)
#define PIN_HIGHSIDE0_EN_FLAGS          (IOPORT_MODE_MUX_B)
#define PIN_HIGHSIDE0_EN_PWM_CHANNEL    (PWM_CHANNEL_0)
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

// Highside 1 pin definitions.
// Net ADC0_4 -> PE04 -> J502 Analog Low, Pin 8 (AD7), AFE0_AD4
// Net HIGHSIDE_1_EN -> PA02 -> J503 Digital Low, Pin 8 (D7), PWMC0_PWMH1
//#define PIN_HIGHSIDE1_EN_GPIO           (PIO_PA2_IDX)
//#define PIN_HIGHSIDE1_EN_FLAGS          (IOPORT_MODE_MUX_A)
//#define PIN_HIGHSIDE1_EN_PWM_CHANNEL    (PWM_CHANNEL_1)
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//#define PIN_HIGHSIDE1_ADC_EOC_IRQ       (AFEC_INTERRUPT_EOC_4)

// Highside 2 pin definitions.
// Net ADC0_6 -> PA17 ->
// Net HIGHSIDE_2_EN -> PA25 -> J507 Digital Extra, Pin 25 (D44)
//#define PIN_HIGHSIDE2_EN_GPIO           ()
//#define PIN_HIGHSIDE2_EN_FLAGS          ()
//#define PIN_HIGHSIDE2_EN_PWM_CHANNEL    ()
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

// Highside 12 pin definitions.
// Net ADC1_6 -> PC31 -> J502 Analog Low, Pin 2 (AD1), AFE1_AD6
// Net HIGHSIDE_12_EN -> PA16 ->
#define PIN_HIGHSIDE12_EN_GPIO           ()
#define PIN_HIGHSIDE12_EN_FLAGS          ()
#define PIN_HIGHSIDE12_EN_PWM_CHANNEL    ()
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

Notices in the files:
sw/src/boards/samv71_xplained_ultra/samv71_xplained_ultra.h:
Copyright (c) 2015-2018 Microchip Technology Inc. and its subsidiaries.
